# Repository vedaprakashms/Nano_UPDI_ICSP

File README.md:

# Nano_UPDI_ICSP
a Arduino nano shield for converting nano to both UPDI or ICSP programer for AVR based MCU

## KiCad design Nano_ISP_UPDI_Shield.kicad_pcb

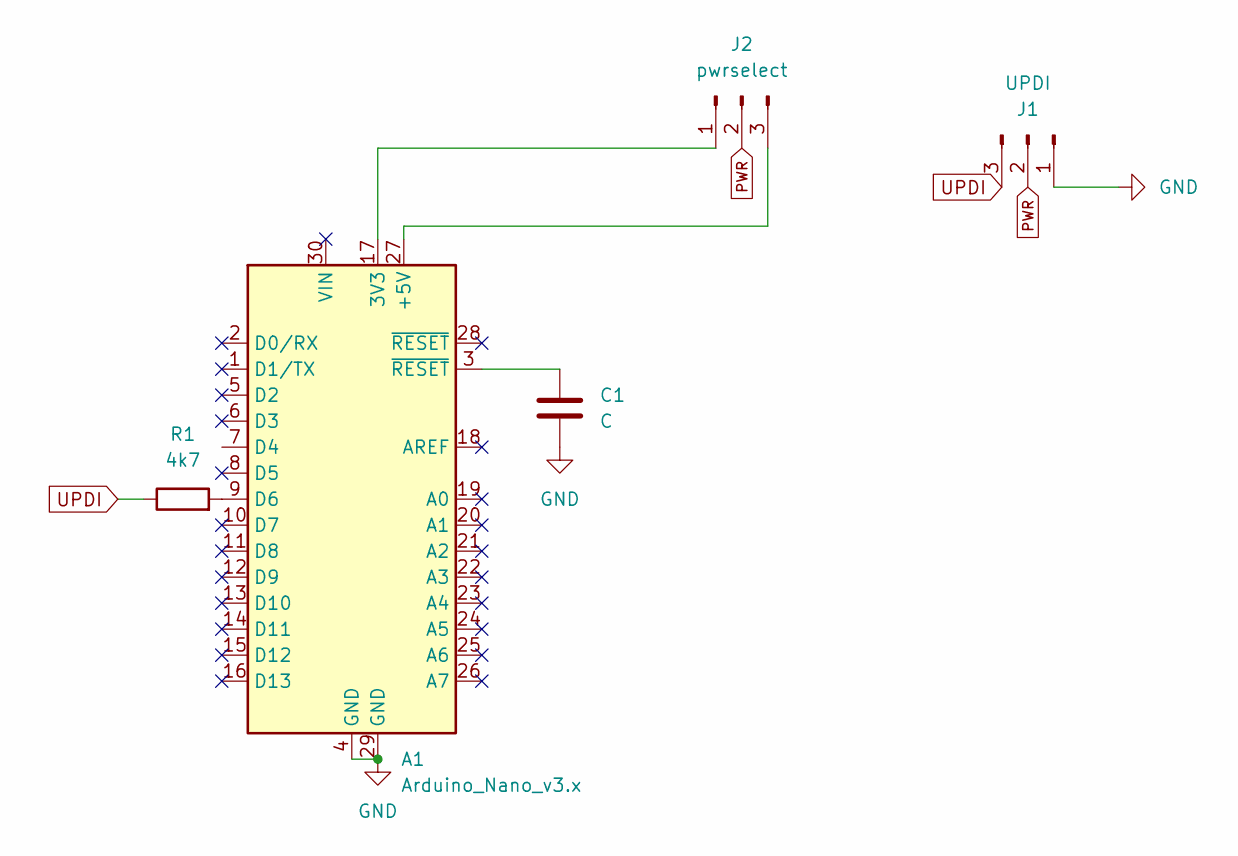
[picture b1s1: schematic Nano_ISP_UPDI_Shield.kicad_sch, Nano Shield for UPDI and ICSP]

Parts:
A1: Arduino_Nano_v3.x; Arduino_Nano_WithMountingHoles
C1: C; C_0805_2012Metric_Pad1.18x1.45mm_HandSolder
J1: UPDI; PinHeader_1x03_P2.54mm_Horizontal
J2: pwrselect; PinHeader_1x03_P2.54mm_Vertical
R1: 4k7; R_0805_2012Metric_Pad1.20x1.40mm_HandSolder

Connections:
GND: A1.4 (GND), A1.29 (GND), C1.2, J1.1
unnamed: A1.17 (3V3), J2.1
unnamed: A1.27 (+5V), J2.3
unnamed: A1.9 (D6), R1.2
unnamed: A1.3 (~RESET), C1.1
PWR: J1.2, J2.2
UPDI: J1.3, R1.1

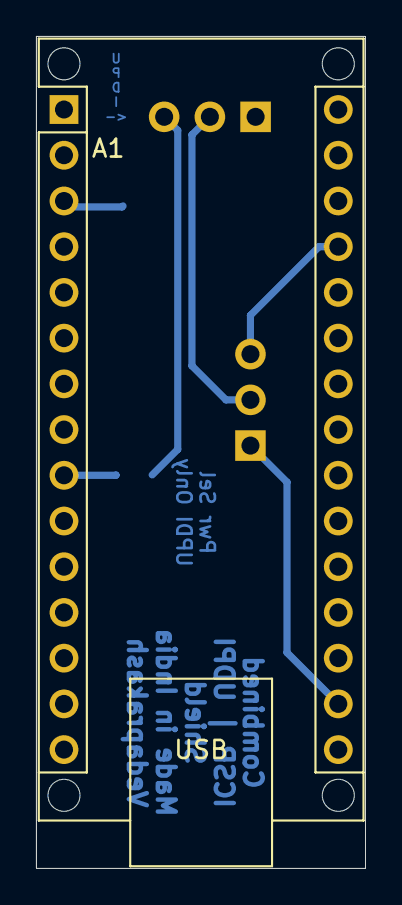
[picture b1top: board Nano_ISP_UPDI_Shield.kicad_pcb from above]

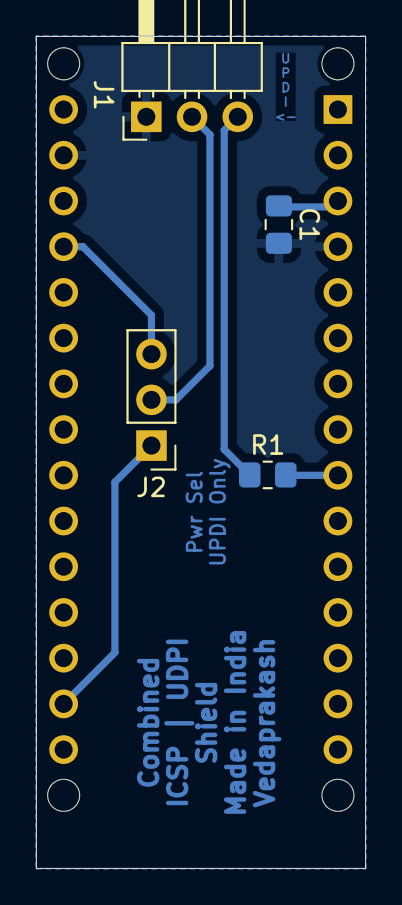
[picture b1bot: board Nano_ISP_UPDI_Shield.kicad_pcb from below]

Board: 2 copper layers, 18.3 x 46.2 mm, 5 parts (4 on the bottom side), 7 nets.

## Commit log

2025-04-25 rev1
2025-05-05 version1
